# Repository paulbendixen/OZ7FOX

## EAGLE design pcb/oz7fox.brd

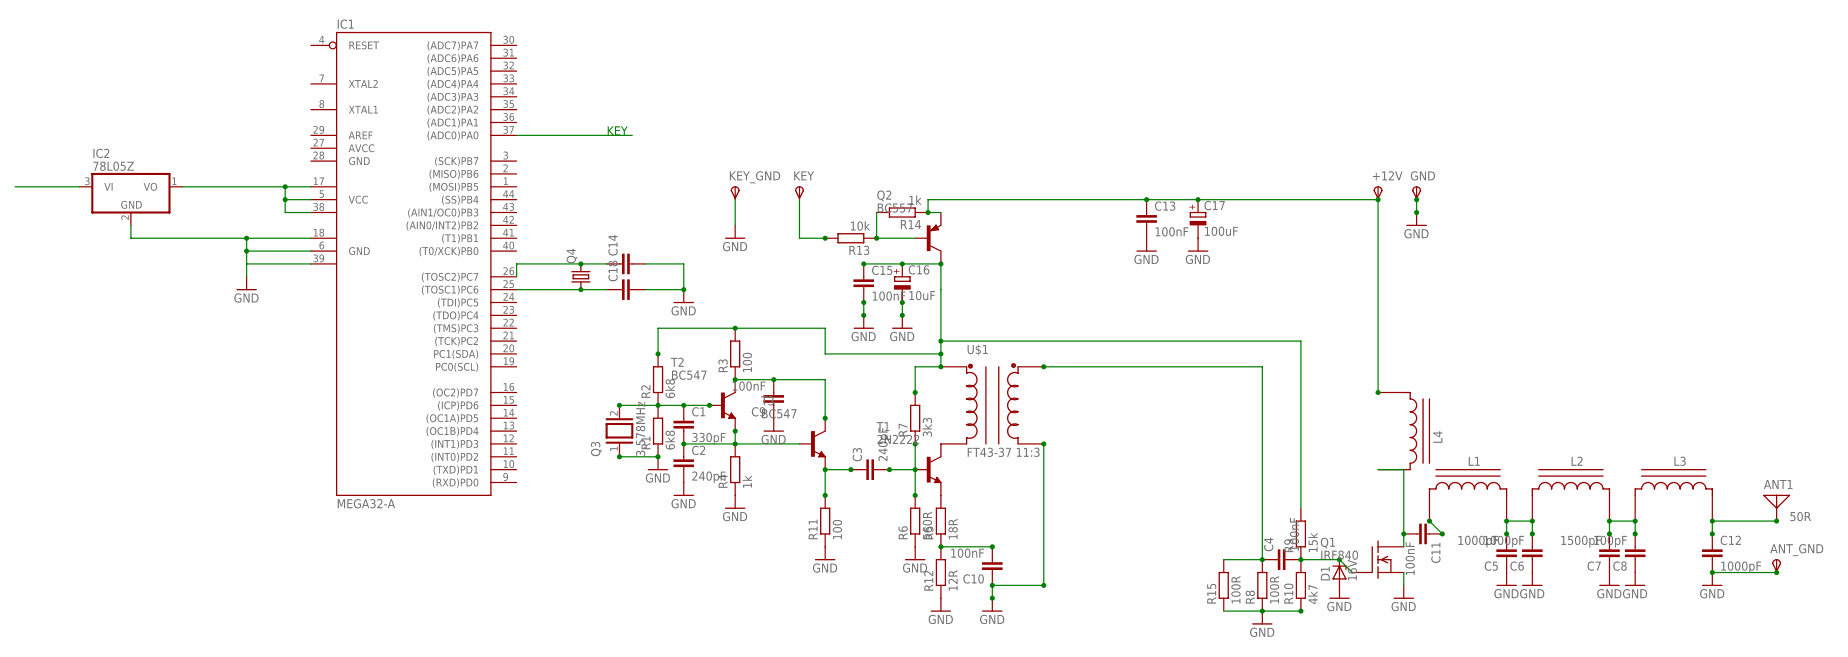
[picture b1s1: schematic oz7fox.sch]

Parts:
+12V: TPSPAD1-20; P1-20
ANT1: 50R; PAD-01
ANT_GND: TPSPAD1-20; P1-20
C1: 330pF; C150-054X183
C2, C3: 240pF; C150-054X183
C4, C11: 100nF; C150-054X183
C5, C6, C12: 1000pF; C150-054X183
C7: 1500pF; C150-054X183
C8: 100pF; C150-054X183
C9, C10, C13, C15: 100nF; C050-025X075
C14, C18: C5/2.5; C5B2.5
C16: 10uF; E5-13
C17: 100uF; E5-13
D1: 16V; ZDIO12.5
GND: TPSPAD1-20; P1-20
IC1: MEGA32-A; TQFP44
IC2: 78L05Z; TO92
KEY: TPSPAD1-20; P1-20
KEY_GND: TPSPAD1-20; P1-20
L1, L2, L3: T37_INDUCTOR
L4: T37-2 16t; T37_INDUCTOR
Q1: IRF840; TO220
Q2: BC557; TO92
Q3: 3,578MHz; Q
Q4: CRYSTALTC26V; TC26V
R1: 6k8; 0207/12
R2: 6k8; 0207/10
R3, R11: 100; 0207/12
R4, R14: 1k; 0207/12
R5: 18R; 0207/12
R6: 560R; 0207/12
R7: 3k3; 0207/12
R8, R15: 100R; 0207/12
R9: 15k; 0207/12
R10: 4k7; 0207/12
R12: 12R; 0207/12
R13: 10k; 0207/12
T1: 2N2222; TO18
T2, T3: BC547; TO92
U$1: FT43-37 11:3; T37_TRANSFORMER

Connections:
12V: +12V.TP, C13.1, C17.+, IC2.3 (VI), L4.CB, Q2.1 (E), R14.1
AVCC: IC1.27 (AVCC)
GND: ANT_GND.TP, C2.2, C5.1, C6.1, C7.1, C8.1, C9.1, C10.1, C12.2, C13.2, C14.2, C15.2, C16.-, C17.-, C18.2, D1.A, GND.TP, IC1.6 (GND), IC1.18 (GND1), IC1.28 (GND), IC1.39 (GND2), IC2.2 (GND), KEY_GND.TP, Q1.3 (S), Q3.1, R1.1, R4.1, R6.1, R8.1, R10.1, R11.1, R12.1, R15.1, U$1.C2A
KEY: IC1.37 ((ADC0)PA0), KEY.TP, R13.2
unnamed: C1.2, C2.1, R4.2, T2.1 (E), T3.2 (B)
unnamed: C11.1, L1.CB
unnamed: C1.1, Q3.2, R1.2, R2.1, T2.2 (B)
unnamed: C9.2, R3.1, T2.3 (C), T3.3 (C)
unnamed: C15.1, C16.+, Q2.3 (C), R2.2, R3.2, R7.2, R9.2, U$1.C1B
unnamed: C3.1, R11.2, T3.1 (E)
unnamed: C11.2, L4.CA, Q1.2 (D)
unnamed: C3.2, R6.2, R7.1, T1.2 (B)
unnamed: R5.2, T1.1 (E)
unnamed: C10.2, R5.1, R12.2
unnamed: T1.3 (C), U$1.C1A
unnamed: C5.2, C6.2, L1.CA, L2.CB
unnamed: IC1.5 (VCC), IC1.17 (VCC1), IC1.38 (VCC2), IC2.1 (VO)
unnamed: C7.2, C8.2, L2.CA, L3.CB
unnamed: C18.1, IC1.25 ((TOSC1)PC6), Q4.1
unnamed: ANT1.1, C12.1, L3.CA
unnamed: C4.1, R8.2, R15.2, U$1.C2B
unnamed: C4.2, D1.C, Q1.1 (G), R9.1, R10.2
unnamed: C14.1, IC1.26 ((TOSC2)PC7), Q4.2
unnamed: Q2.2 (B), R13.1, R14.2

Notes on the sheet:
KEY

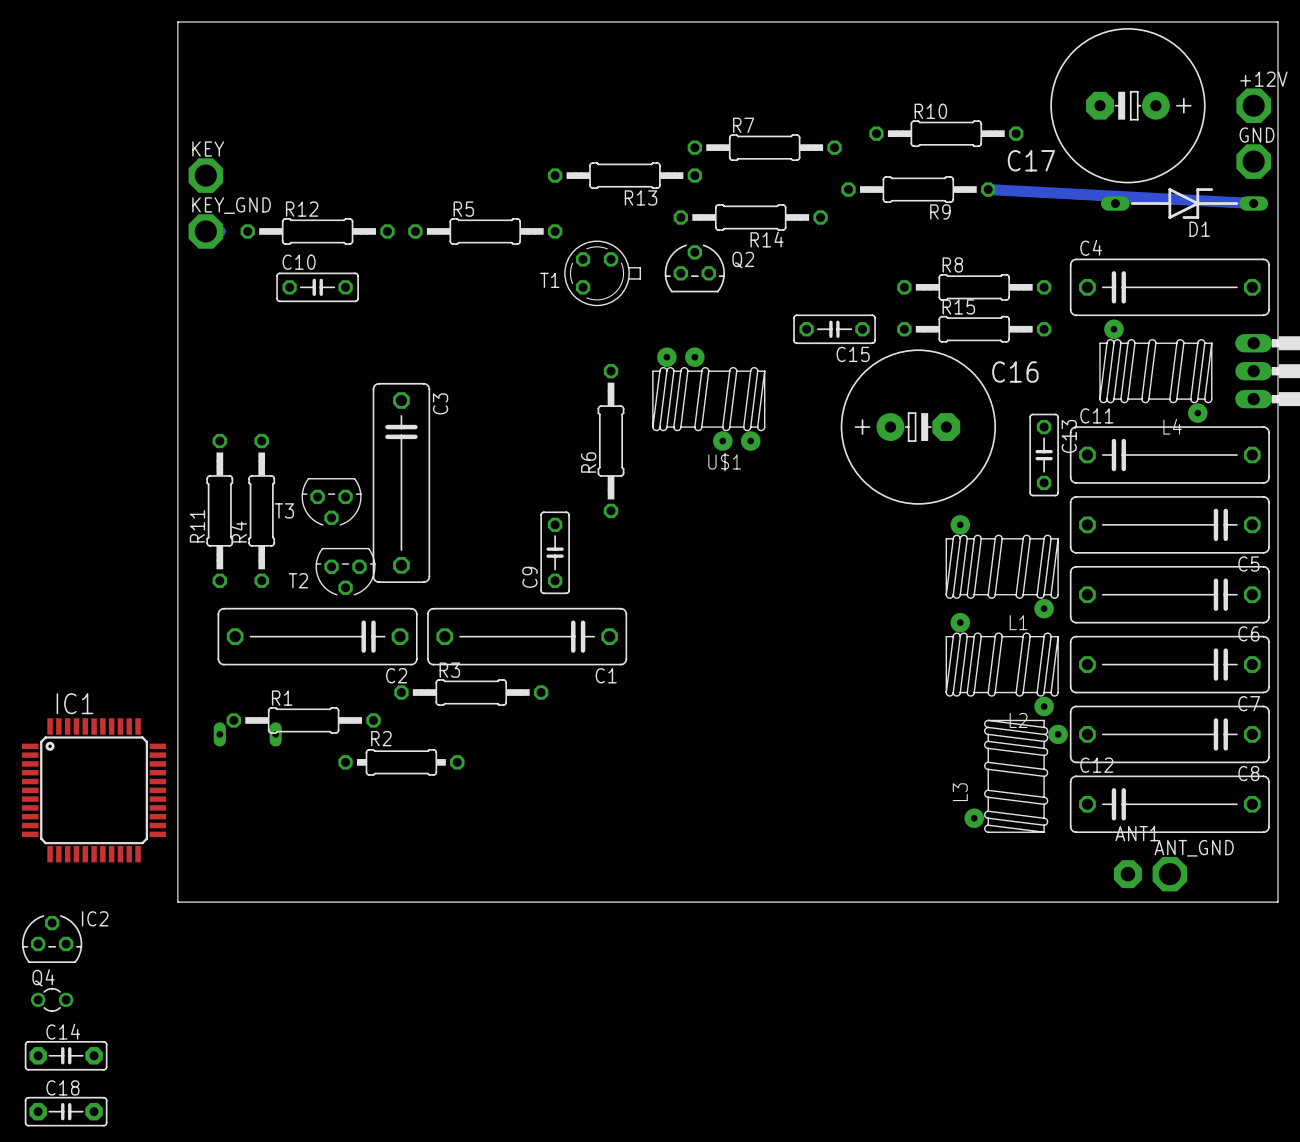
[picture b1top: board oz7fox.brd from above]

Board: 2 copper layers, 100.0 x 80.0 mm, 54 parts (1 on the bottom side), 23 nets.

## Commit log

2012-11-20 Added keying still needs to work for anything
2012-11-27 Der skal rodes mere med Makefilen før den gider kompilere
2012-11-27 Compiles and burns using the new Makefile, but does not work yet
2012-12-11 Leds actually blink now
    The leds now actually blink.
    The problem was the way the registers were set as well as the need for
    the correct registers to be set.
2012-12-11 Made the morse coder morse code - do not connect to radio
    Added code to send morse code, consider making it more user friendly.
    Changed the Makefile to use the correct programmer (stk500v2) so that
    programming is done faster.
    The test program now sends out SOS two times with letter and word
    spacing between.
    NEVER SEND OUT SOS FOR TESTING!!!
2012-12-12 Changed the period of the morse (40wpm)
    Changed the period to use 40 wpm instead of arbitrary.
    Used on the notion that paris is 43 chars long.
    Made the opportunity for setting in the fox at the correct point in the
    sequence.
2013-01-08 Something doesn't work, but I'm tired
2013-02-14 Wakeup timer works, timing is wrong thoug
    Also changed the morse code to send out OZ7FOX instead of SOS.
    Some debug LEDs still remain in this version.
2013-02-16 Added TODO
    ... to drink coffee ;)
2013-02-16 Fixed the timing problems
    Also made the timing variables a bit more opaque and added some comments
    and references to the datasheet
2013-02-16 Change in the way Morse characters are handled
    Rewrote the character sending system to be struct-based.
    Morse characters now have their own datatype morse_char_t
    which can be handled directly by sendChar().
2013-02-16 Made the morse part be longer (about one minute)
2013-02-16 Minor changes and comments.
2013-02-16 Moved timing related functions to timer.c/h
    Fixed the timing problem, it is now synchronized
    The project is now functional, the rest should just be pretty printing
2013-02-16 Refactored main.c and removed unused funtionality
    Cleaned up main method in main.c and factored out
    some of the functionality to functions to
    improve readability of the code.
2013-02-16 Added some documentation
2013-02-16 Rewrote handling of timer counts.
    Timer count is now calculated by a macro in globals.h
    The timer count MUST NOT exceed 2^16. This is NOT checked at
    compile time, so use of the macro should be done with caution.
2013-02-16 Rewrote handling of morse ticks in key and main.
    ... or something....
2013-02-16 Made a new frontpage of the documentation
2013-02-16 Committing in order to merge
2013-02-16 Fixed declaration of delay() function.
2013-02-16 We've reached a working version
    Now we just need to add comments so that people can read our code.
    Also at some time (perhaps 1.2) It would be nice to be able to select
    what fox this is ;)
2013-02-16 Mostly doctumentation
    Also specified the TODO
2013-02-16 Added doxygen comments and fixed minor bugs.
    Elaborated on doxygen-related comments, primarily in main.c.
    Fixed minor bug in key.c.
2013-02-17 Added a README because github wanted it
2013-02-17 Moved the doxygen comment in main.c so it gets in
    Also corrected the atrocious space indenting Boris had done
2013-02-17 More indentation corrections
    Found out that Boris had done even more of his atrocious space indenting
    in other files, so I had to fix that also.
2013-02-18 Refactored timing of morse, wrote comments
    all: All functions that measure time in morse ticks now use the
    type ticks_t to reflect that we deal in morse ticks
    rather than clock cycles or milliseconds.
    key.h:
    - The macro assignments that turn the morse pin on and off
    now have their own macros MORSE_ON and MORSE_OFF.
2013-02-18 Header file and #include cleanup
    Cleaned up #include statements and header file stuff.
2013-02-18 Fixed indentation
    I have now fixed my VIM so that it handles indentations
    by using the TAB character, like its creator paulbendixen
    has specified. Conflicts with my spaces-based indentation
    is visible once tabspace is interpreted differently :(
2013-02-18 Minor refactoring + suppport for intl. fox id
    main.c:
    - the sendFoxID funktion now supports the sending of
    fox id 1-5 (0-4) if the #define INTERNATIONAL_FOX_ID
    is present.
    - All doxygen comments are now prefixed with '*' for multi-line comments
    key.c
2013-02-19 Added main.h - d*mn!
    Baah½
2013-02-19 Added .vimrc with project-specific settings.
    Enable this by adding the following lines to your vimrc:
    set exrc " enable per-directory .vimrc files
    set secure " disable unsafe commands in local .vimrc files
    See more information at:
    http://damien.lespiau.name/blog/2009/03/18/per-project-vimrc/
2013-02-19 Total number of foxes = 5, Fox4 = four
2013-03-06 Increased pause between callsign and id
    Increased pause between callsign and id to full inter-word-space
    to make it more easy to distinguish from the callsign when listening.
2013-03-12 Removed faulty .vimrc
    There is a code standard for this repository
    Tabbing is done using tabs and is eight spaces
    Allman braces are used, please respect this
2013-03-17 Changed platform and added string sending
    First change is that the target is now the MEGA32 controller.
    This is the one on the AVR stamp that Bertho has made available at
    http://www.vagrearg.org/content/avrpicstamp
    The second change is that by doing an arary of morse components
    it is now possible to send an actual string.
    I'm beginning to think we might need some kind of unit testing,
2013-03-17 Forgot last update of file main.c
    Doh!
2013-04-09 Added the AVR ISP mkII programmer to the Makefile
2013-04-09 Moved the code to subfolder and added a pcb dir
    All code is move to the avrcode subdirectory
    The PCB is added to the pcb subdirectory
2019-10-19 AVRCode: Added fox selector
2020-08-28 AVR code: Made the foxes after one work
